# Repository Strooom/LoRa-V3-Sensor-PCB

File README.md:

# LoRa-V3-sensor PCB

KiCAD design files for the LoRa-V3-Sensor-PCB.

This is a small PCB with sensors which plugs into the LoRa-V3-PCB. The purpose is the be able to easily replace the sensors with calibrated ones or upgrade the LoRa-V3 device with newer sensors.

## Renders
### Front

### Back

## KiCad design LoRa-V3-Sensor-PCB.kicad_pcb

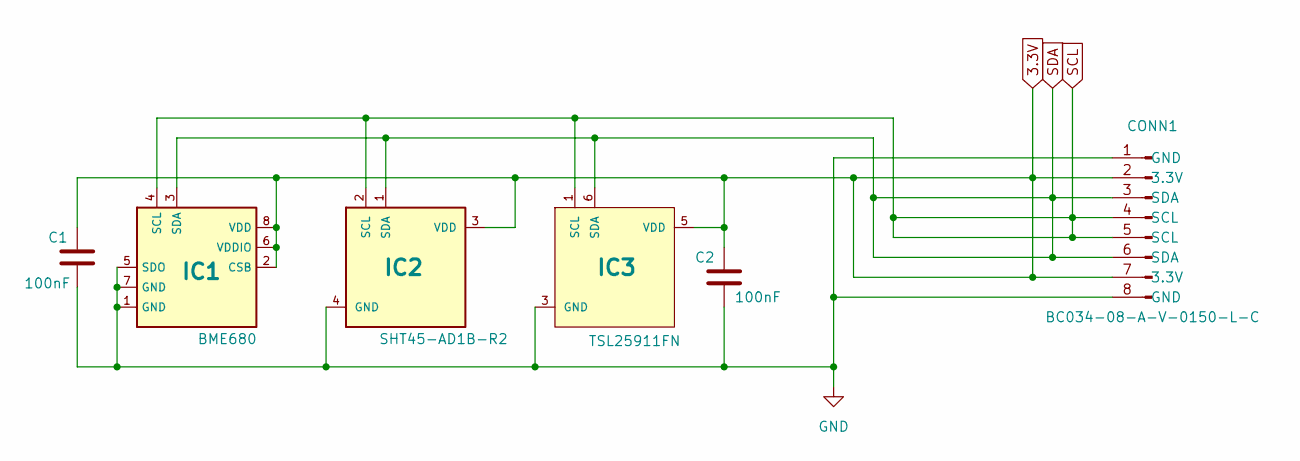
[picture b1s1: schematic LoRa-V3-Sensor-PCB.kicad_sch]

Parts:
C1, C2: 100nF; C_0603_nominal; manufacturerPartNumber CGA3E2X7R1E104K080AA
CONN1: Conn_01x08_Pin; GCT_BC034-08-A-V-0150-L-C; manufacturerPartNumber BC034-08-A-V-0150-L-C
IC1: BME680; BME68X; manufacturerPartNumber BME680
IC2: SHT45-AD1B-R2; SHT4X; manufacturerPartNumber SHT45-AD1B-R2
IC3: TSL25911FN; TSL2591; manufacturerPartNumber TSL25911FN

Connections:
3.3V: C1.1, C2.1, CONN1.2 (3.3V), CONN1.7 (3.3V), IC1.2 (CSB), IC1.6 (VDDIO), IC1.8 (VDD), IC2.3 (VDD), IC3.5 (VDD)
GND: C1.2, C2.2, CONN1.1 (GND), CONN1.8 (GND), IC1.1 (GND), IC1.5 (SDO), IC1.7 (GND), IC2.4 (GND), IC3.3 (GND)
SCL: CONN1.4 (SCL), CONN1.5 (SCL), IC1.4 (SCL), IC2.2 (SCL), IC3.1 (SCL)
SDA: CONN1.3 (SDA), CONN1.6 (SDA), IC1.3 (SDA), IC2.1 (SDA), IC3.6 (SDA)

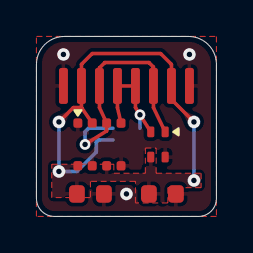
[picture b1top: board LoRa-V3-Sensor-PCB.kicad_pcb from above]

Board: 2 copper layers, 10.0 x 10.0 mm, 6 parts (1 on the bottom side), 4 nets.

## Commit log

2025-04-16 remove unwanted fields
2025-04-16 add workflow generated files
2025-04-16 change BME680 to 690
2025-04-16 fix missing 3d model for C0603
2025-04-16 set rounding radius to 1.55 mm
2025-04-16 move ic3 to back side
2025-04-23 add back render and readme
2025-04-23 move readme to root of repo
2025-07-02 improve pin naming of connector
2025-10-15 improve workflow
2025-10-15 fix kibot workflow error
2025-10-15 split release into a separate workflow
2025-10-15 add mpn as field
    this is required as Aisler needs this specific field name and cannot read the already existing manufacturerPartNumber field
2025-10-15 updates bom from schematic to board
